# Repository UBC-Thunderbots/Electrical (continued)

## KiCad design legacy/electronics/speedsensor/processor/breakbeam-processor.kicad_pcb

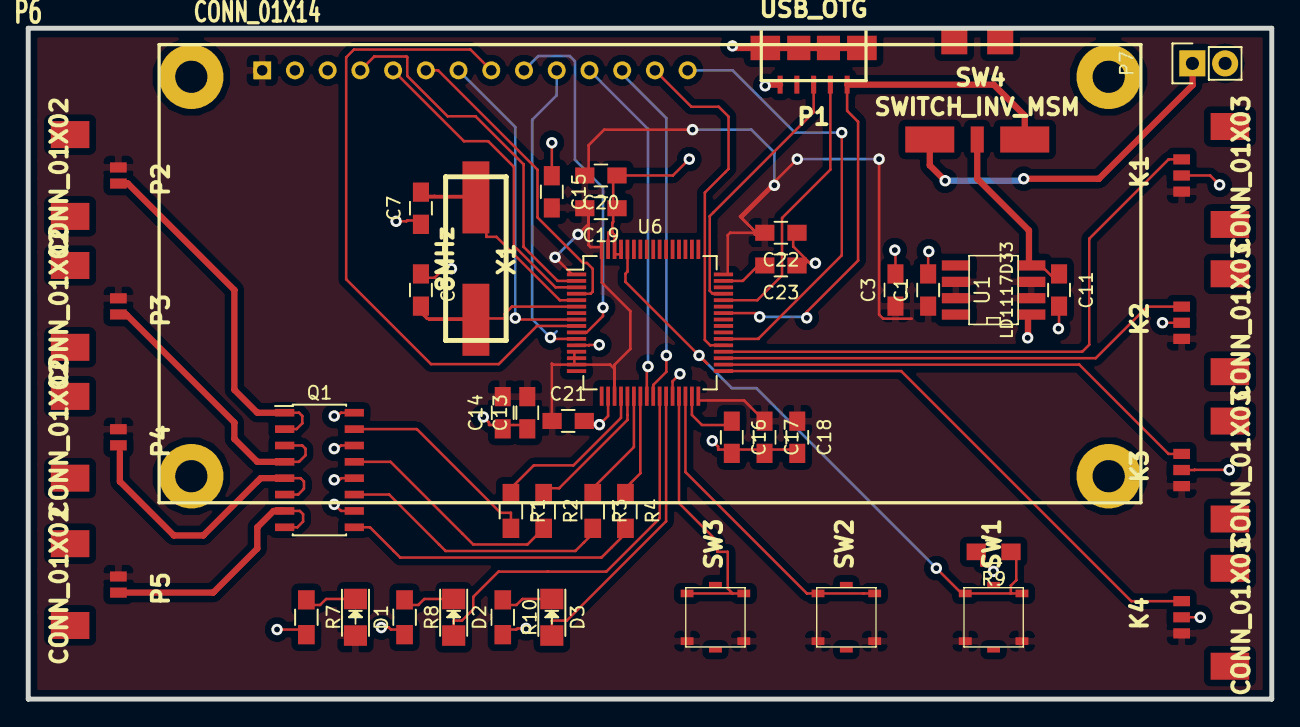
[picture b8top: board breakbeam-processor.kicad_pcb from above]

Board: 2 copper layers, 96.5 x 52.1 mm, 46 parts (0 on the bottom side), 46 nets.

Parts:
C1, C16, C23: 2.2uF; C_0805_HandSoldering
C3, C15, C17, C20, C21, C22: 100nF; C_0805_HandSoldering
C7, C8: 15pF; C_0805_HandSoldering
C11, C13: 1uF; C_0805_HandSoldering
C14: 10nF; C_0805_HandSoldering
C18, C19: 4.7uF; C_0805_HandSoldering
D1: POWER_LED; LED_1206
D2: Green-LED; LED_1206
D3: green-LED; LED_1206
K1, K2, K3, K4: CONN_01X03; connector_0_49_in_3pin
P1: USB_OTG; USB_MICRO_B_SPEED_SENSOR
P2, P3, P4, P5: CONN_01X02; connector_0_49_in_2pin
P6: CONN_01X14; LCD_screen
P7: CONN_01X02; Pin_Header_Straight_1x02
Q1: MMPQ3904; SOIC-16_3.9x9.9mm_Pitch1.27mm
R1, R2, R3, R4, R7, R8, R10: R; R_0805_HandSoldering
R9: 1kR; R_0805_HandSoldering
SW1, SW2, SW3: SW_PUSH; SW_SMD_TAC
SW4: SWITCH_INV_MSM; SW_ROCKER_SP3T
U1: LD1117D33; SO8E
U6: STM32F405RXT; TQFP-64_10x10mm_Pitch0.5mm
X1: 8MHz; HC49US

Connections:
+3V3: C1.1, C3.1, C13.2, C14.2, C15.2, C17.1, C18.1, C19.2, C20.2, C21.1, C22.2, D1.2, K1.1, K2.1, K3.1, K4.1, P2.1, P3.1, P4.1, P5.1, P6.1, SW1.2, SW2.2, SW3.2, U1.2, U1.3, U1.6, U1.7, U6.1, U6.13, U6.14, U6.15, U6.19, U6.32, U6.48, U6.64
+5V: P1.1, SW4.3, U6.42
+BATT: P7.1, SW4.1
GND: C1.2, C3.2, C7.1, C8.1, C11.2, C13.1, C14.1, C15.1, C16.2, C17.2, C18.2, C19.1, C20.1, C21.2, C22.1, C23.1, K1.2, K2.2, K3.2, K4.2, P1.5, P1.6, P6.2, P7.2, Q1.10, Q1.12, Q1.14, Q1.16, R7.2, R8.2, R9.2, R10.2, U1.1, U6.12, U6.18, U6.28, U6.61, U6.62, U6.63
unnamed: C7.2, U6.5, X1.1
unnamed: C8.2, U6.6, X1.2
unnamed: C11.1, SW4.2, U1.4
unnamed: C16.1, U6.31
unnamed: C23.2, U6.47
unnamed: D1.1, R7.1
unnamed: D2.1, R8.1
unnamed: D2.2, U6.26
unnamed: D3.1, R10.1
unnamed: D3.2, U6.27
unnamed: K1.3, U6.36
unnamed: K2.3, U6.35
unnamed: K3.3, U6.34
unnamed: K4.3, U6.33
unnamed: P1.2, U6.44
unnamed: P1.3, U6.45
unnamed: P2.2, Q1.1, Q1.2
unnamed: P3.2, Q1.3, Q1.4
unnamed: P4.2, Q1.5, Q1.6
unnamed: P5.2, Q1.7, Q1.8
unnamed: P6.4, U6.2
unnamed: P6.5, U6.3
unnamed: P6.6, U6.4
unnamed: P6.7, U6.8
unnamed: P6.8, U6.9
unnamed: P6.9, U6.10
unnamed: P6.10, U6.11
unnamed: P6.11, U6.24
unnamed: P6.12, U6.25
unnamed: P6.13, U6.37
unnamed: P6.14, U6.38
unnamed: Q1.9, R4.2
unnamed: Q1.11, R3.2
unnamed: Q1.13, R2.2
unnamed: Q1.15, R1.2
unnamed: R1.1, U6.20
unnamed: R2.1, U6.21
unnamed: R3.1, U6.22
unnamed: R4.1, U6.23
unnamed: R9.1, SW1.1, U6.60
unnamed: SW2.1, U6.30
unnamed: SW3.1, U6.29

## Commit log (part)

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2015-10-10 Added software goals
2015-10-12 Adding 2.2uF caps to VCAP.
2015-10-14 Fix USB turnaround time based on table in new reference manual revision.
2015-10-14 Tidy up, (hopefully) robustify, and tweak priorities on some DMA transfers.
2015-10-17 Add USB specification.
2015-10-17 Fixed error with conversions.
2015-10-17 add matlab script to read lps data coming from a pipe
2015-10-21 Upgrade to FreeRTOS 8.2.3.
2015-10-25 Implement null drive backend and bin/nulltest which can be used to explore MRFTest UI without a dongle.
2015-10-25 Fix warning.
2015-10-30 Eliminate dynamic creation and deletion of tasks and IPC objects in dongle code, instead creating them once at startup.
2015-10-30 Fix line endings.
2015-10-30 Use direct-to-task notifications in the dongle to eliminate a bunch of semaphores and global variables. See ticket:1503.
2015-10-31 Remove unnecessary DSB.
2015-10-31 Statically, instead of dynamically, allocate stacks in the dongle.
2015-11-01 Migrate CDCACM to use direct-to-task notifications and to reuse the task instead of deleting and recreating it. See ticket:1503.
2015-11-07 Fix bug in drive packet encoding.
2015-11-07 Eliminate uses of vTaskDelete in main robot firmware.
2015-11-08 change pin mapping for lps
2015-11-08 Replace the full dynamic stack allocator with a simple forward-only allocator now that we never delete tasks.
2015-11-08 Remove unnecessary Newlib reentrancy structures from FreeRTOS TCBs.
2015-11-08 Statically allocate more task stacks.
2015-11-11 New datasheet revision.
2015-11-14 Added CMDvsMRL logs
2015-11-14 Eliminate deletion of some IPC objects.
2015-11-15 Eliminate a dynamic stack allocation and some IPC object deletions.
2015-11-15 Get rid of the homebrew heap management and migrate to FreeRTOS heap implementation #1 instead.
2015-11-15 Enable multi-threaded core dumps in dongle code.
2015-11-21 Remove old debug code.
2015-11-21 Replace a bunch of module-specific semaphores used for shutdown sequencing with single shutdown- or mode-change-sequencing semaphores shared across all modules.
2015-11-21 calibrated lps output
2015-11-21 Updated Makefile to include required libraries.
2015-11-21 Added required files for USB use.
2015-11-22 Use direct-to-task notifications where it makes sense. Fixes ticket:1503.
2015-11-22 added logo as png
2015-11-22 matlab code used to computer calibration constant for lps
2015-11-22 forgot to turn off printing
2015-11-22 added log message for lps value, remember to put this in log format
2015-11-28 #include "ai/hl/stp/play/simple_play.h" #include "ai/hl/stp/tactic/block.h" #include "ai/hl/stp/tactic/pass.h" #include "ai/hl/stp/tactic/intercept.h" #include "ai/hl/stp/tactic/offend.h" #include "a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
    using AI::HL::STP::Enemy;
    namespace Predicates = AI::HL::STP::Predicates;
    /**
    * Pass, defenders have higher priority than passers
    */
    BEGIN_PLAY(TriDefense2015)
2015-12-05 robot can sing
2016-01-15 Do read retries in promiscuous mode to handle SPI transfer errors. Fixes ticket:1432.
2016-01-16 Make Box<T> a union-like class using an aonymous union instead of a named sub-union.
2016-01-16 Use perfect forwarding for Box<T>::create.
2016-01-22 Add test bench for arbiter module. See ticket:1279.
2016-01-22 Remove unused library reference.
2016-01-24 Adding dribbler rpm as a controllable parameter for dribble primitive.
2016-01-24 Adding 100 nylon screws to the mcmaster order.
2016-01-30 Catch simulation code
2016-01-30 fixed naming convention for files...
2016-01-30 Change dribbler control from constant voltage to constant RPM.
2016-01-31 Changing dribbler's constant speed controller so PWM changes scales with error
2016-02-06 fixed valgrind uninitialized memory in PrimitiveInfo
2016-02-06 Changed the logic of the catch primitive.
2016-02-06 Added logging.
2016-02-13 Merged from trunk
2016-02-13 wups
2016-02-19 updated particle filter to use breakbeam for ball detection
2016-02-19 undid changes to project.mk file that commented out coroutines
2016-02-27 - added poster
2016-03-03 Remove out-of-date comment.
2016-03-12 Include runtime-mode PID in DFU file instead of DFU-mode PID, as newer versions of dfu-util require.
2016-03-19 Changes for camera's ICCB interface.
2016-04-15 Camera: data stored in SRAM via DMA.
2016-04-23 Fix broken include.
2016-04-23 changed math.h to cmath in particle filter (getting build errors)
2016-05-07 Add Kalman filter framework
2016-05-21 Use alternate setting names instead of numbers and remove configuration and interface numbers when invoking `dfu-util` for DFU (non-DfuSe) mode, eliminating the over-strict matching that otherwise ha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
2016-05-21 Add a couple of missing SD card serial numbers.
2016-05-21 Implement transmit cancellation to avoid getting stuck during system shutdown if the radio is misbehaving.
2016-05-21 Eliminate some unnecessary indirection through FreeRTOS when dealing with failure to transmit an autokick confirmation packet.
2016-05-21 Adjust energy detection threshold for MD part.
2016-05-21 updated linux.txt
2016-05-28 Current camera code. Compiles and uses the registers in the right datasheet. Captured image is still weird.
2016-05-28 Updated the camera register settings
2016-06-11 Use LevelBar instead of ProgressBar for things that are not progress. Fixes ticket:1594.
2016-06-11 Updated inventory and added notes for needed parts
2016-06-11 added parts to order
2016-06-18 Kick up to a higher sample time in order to accommodate the larger resistor divider being planned on the new chicker boards.
2016-06-25 Add missing CLREX in context switching code.
2016-06-25 Fix capacitor voltage calculation for new resistor divider.
2016-06-25 Reduce power level of safe discharge procedure as new chicker board with fewer capacitors doesn’t need so much.
2016-06-28 move navigator info to debug, move robot behind ball to shoot
2016-06-28 Fix typo.
2016-06-28 Implement noise squelching to avoid false stuck notifications on the dribbler Hall sensors during kicking and chipping.
2016-06-28 Remove unnecessary CLREX. It is implicitly done on every exception entry.
2016-06-28 update config
2016-06-28 autoplacement refbox
2016-06-28 Use assigned freqencies.
2016-06-28 replaced old intercept tactic with new intercept_v2 tactic in plays
2016-06-29 made intercept_v2 an active tactic, and changed intercept location for when ball is slow/stationary
2016-06-30 Stop crashing on full SD cards.
2016-06-30 Kill the Hall sensor noise squelching code; it was horribly broken.
2016-06-30 Use current instead of latched Hall sensor stuck status for deciding whether to drive motor or not.
2016-07-01 Eliminate broken function `dribbler_set_power`.
2016-07-01 Allow dribbler to be coasted.
2016-07-01 Remove some LPS-related printing stuff and do a bit of tidying.
2016-07-01 Clarify some comments and clean up a barrier.
2016-07-01 Reboot instead of hanging after a crash, and report it as an error to the annunciator panel.
2016-07-01 Check for a second dongle sharing a channel+PAN.
2016-07-01 Implement averaging filter for break-beam and LPS ADC readings to filter out noise from motors.
2016-07-01 reverting dribble primitive max accel
2016-07-01 Log break beam difference to SD card instead of absolute value.
2016-07-01 Fix crash on mode change.
2016-07-01 Fix some sensitivity related code.
2016-07-01 Remove ICB debugging code.
2016-07-01 Implement liveness checking of the FPGA.
2016-07-02 Reinitialize the radio if no packets are seen for a second. Seems to fix hangs.
2016-08-16 New version of Spartan 6 configuration manual.
2016-10-01 added instructions to downgrade the coroutine library to 1.54
2016-10-01 fixed duplicate parameter error
2016-10-01 added instructions to autoremove libboost-1.58 libraries
2016-10-01 modified coroutine instructions again..........
2016-10-15 Added an extrusion to the assembly, which represents allowable drivetrain size.
2016-10-15 added flag for single or continuous calling of MP in test navigator
2016-10-22 Fix crazy file organization.
2016-10-22 Fix library path.
2016-11-05 motor control paper
2016-11-05 Temporary changes to voltage clamp
2016-11-12 New Kicker Function -updated for 3 capacitors
2017-01-14 Set some missing properties.
2017-01-14 Fixed resistor footprint.
2017-01-14 Added in the rules for the updated speedsensor for USB reading.
2017-01-21 Enlarge small vias on high-current traces.
2017-01-21 Route high current better and increase clearance.
2017-01-21 Remove old screw.
2017-01-21 fixed bug where enemy and friendly_corner_pos had the wrong y-values
2017-02-05 added logic for indirect chipping. Now includes shooting, chipping at the net, chip and chase, and ricochet for another kick
2017-02-11 Document logic behind power switch.
2017-03-11 Vincent's test code for clustering ball filter
2017-03-25 updated default part and value pairs
2017-03-25 Started stub.
2017-03-25 Added the chicker parts to the defaults section.
2017-03-25 added method for converting kicad4 csv to lst file
2017-03-25 Fixed incorrect spelling.
2017-03-25 fixed quote slicing
2017-03-25 Added 6-pin connector.
2017-03-25 Fixed R4 reference.
2017-03-31 updated depreciated read method for URL info request.
2017-04-01 updated LED part label
2017-04-01 updated inventory.
2017-04-08 Changed 2.2k resistor default.
2017-04-08 Edited to add non-digikey parts to generated BOM.
2017-04-08 Update OSC inventory.
2017-04-23 Updated chicker board inductor default.
2017-05-07 merged new catching and shooting code
2017-06-04 Fixed DNP capacitor and 15A_SLOW fuse issue on main board.
2017-06-17 Added debug line for print statements.
2017-06-17 Added debug checks on sd image check in util.c.
2017-06-17 Added check to ensure proper alignment of data blocks read.
2017-06-17 Remove unnecessary length alignment check.
2017-07-02 Removed default value for 5A because different fuses are used on the main and chicker boards.
2017-07-02 merged new particle filter
2017-07-08 reverted particle filter merge
2017-07-16 Removed debug code.
2017-11-18 Add new directory
2018-01-27 Latest Altium Folder
2018-04-23 Upload New File
2018-04-23 Main Board Redo in Altium
2018-05-05 finished chicker schematic. Next step: validating library sharing
2018-05-05 library transfer validated. next step: library cleanup
2018-05-15 PCB for the chicker board
2018-05-17 Final Chicker PCB and Gerber files
2018-05-25 gerber files for fixed chicker pcb
2018-06-02 fixed gerber files and outline file (.gm14)
2018-06-02 Added Proper Dongle Copy
2018-09-28 repo cleanup and addition of .gitignore
2018-11-03 FPGA_Project: Initial files needed to run project
2019-02-02 main.Intlib
2019-02-02 Motor Driver Board
2019-02-02 Work in Progress
2019-03-20 pcb mostly finished
2019-09-06 Moved old to legacy dir
2019-09-06 signing test
2019-09-07 Fixed relative links
2019-10-09 Initial commit for models dir
2019-10-23 First iteration of electromagnetic force solenoid model
2019-10-26 Created motor driver board and power distribution board
2019-10-30 Updated model with camel case
2019-10-30 Removed duplicate file
2019-11-02 WIP test file
2019-11-02 moved everything into individual functions
2019-11-23 Docstrings
    Added docstrings to all methods/functions
2019-12-23 is this how i use git idk
2019-12-30 added circle, square, rectangle
2019-12-31 fixed a constant
2020-01-11 Fixed constants, updated model with Tkinter
2020-01-12 changed wire gauge to drop down menu. circle, rect, square complete
2020-02-15 this is the magwire code from geophysik https://www.geophysik.uni-muenchen.de/~wack/teaching/Python/source/magwire/
2020-03-07 New awg_data.json file (removed another category known as mm because we assume result is in mm)
    removed another category known as mm because we assume the result is in mm
2020-05-24 clarify fast-forwards
2020-05-24 Fix ff bug, add some helpful messages
2020-05-24 Update config and gitignore to add all the repos
2020-06-01 Add a warning if the repo didn't actually update
    git pull --ff-only sometimes doesn't actually move the branch pointer.
    We should at least tell the user.
2020-06-07 Finalize moving docs
2020-06-08 Write a setup script for this repository
    Currently implemented:
    * Clone all the repos
    * Install hooks in each one
    * Automatically manage gitignore
2020-07-11 Small fix
